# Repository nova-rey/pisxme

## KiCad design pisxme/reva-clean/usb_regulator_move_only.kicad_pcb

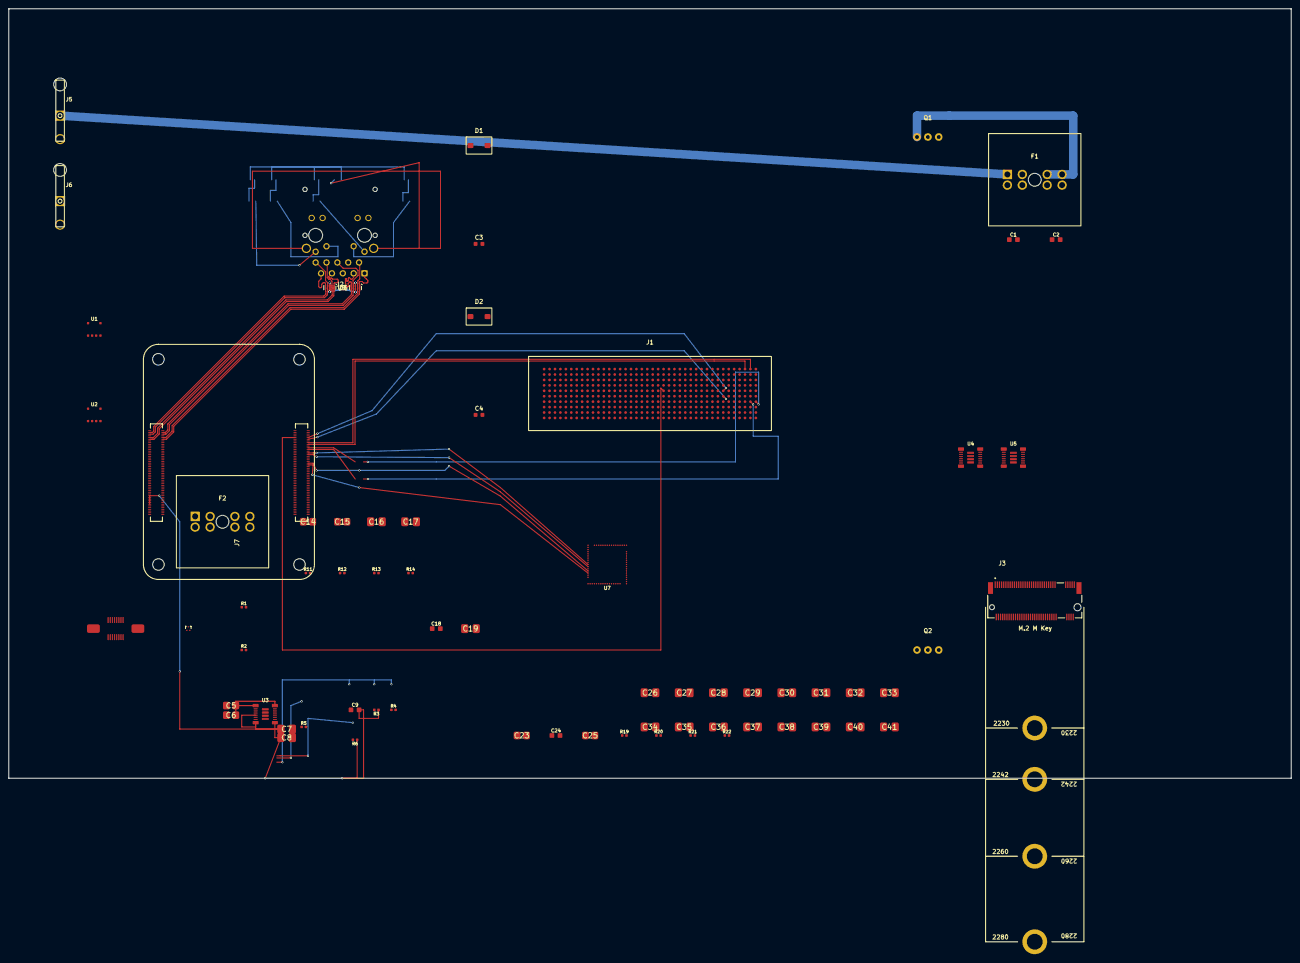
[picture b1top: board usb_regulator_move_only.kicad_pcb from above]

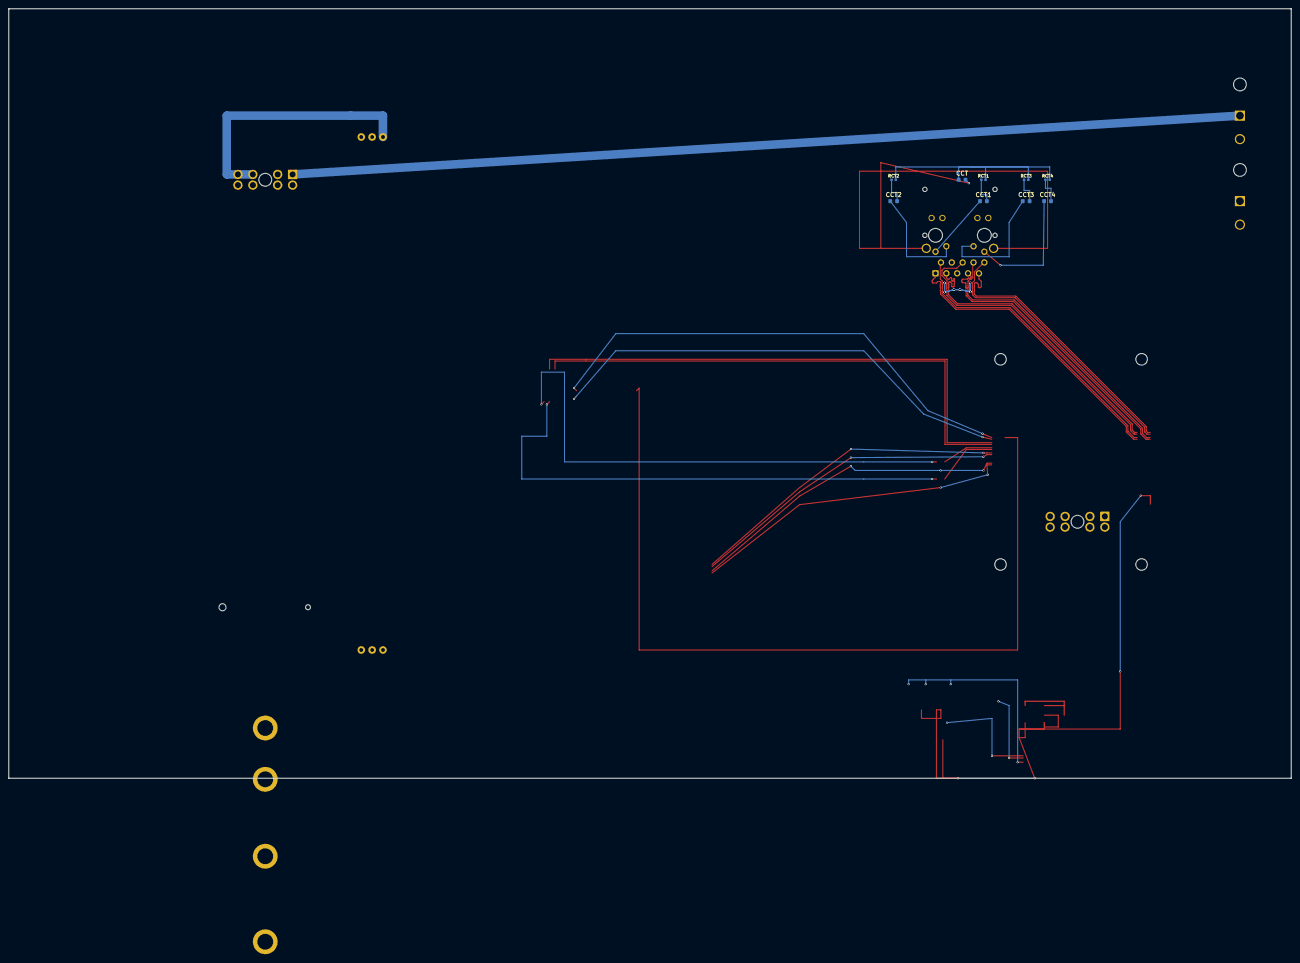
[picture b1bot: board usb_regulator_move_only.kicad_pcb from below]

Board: 6 copper layers, 300.0 x 180.0 mm, 80 parts (11 on the bottom side), 63 nets.

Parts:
C1, C2, C9, C18, C24: C_0805_2012Metric
C3, C4: C_0603_1608Metric
C5, C6, C14, C15, C23, C25: C_1206_3216Metric
C7, C8, C16, C17, C19, C26, C27, C28, C29, C30, C31, C32, C33, C34, C35, C36, C37, C38, C39, C40, C41: C_1210_3225Metric
CCT, CCT1, CCT2, CCT3, CCT4: C_0603_1608Metric
D1, D2: SMBJ18A; TVS_SMBJ18A_DO214AA
F1, F2: 178.6165.0001; ATO_FuseHolder_17861650001
J1: 74221-101LF; PiSXMeRevAClean_SXM2_74221_101LF
J2: A70-112-331N126; EDAC_A70_112_331N126
J3: JAE SM3ZS067U410ABR1000 B-key SATA socket; JAE_SM3ZS067U410ABR1000_BKEY
J4: Amphenol 10171746-00021LF USB-C USB2 SERVICE; USB_C_SERVICE_10171746
J5, J6: 0039300020; Molex_0039300020_5569_2P_RA
J7: Raspberry-Pi-5-Compute-Module; PiSXMeRevAClean_Raspberry_Pi_5_Compute_Module
MECH_M2_2280: JAE SM3ZS067U410ABR1000 / 2280 card envelope; M2_2280_RETENTION_ENVELOPE
Q1, Q2: CSD19536KCS; CSD19536KCS_TO220
R1, R2, R3, R4, R5, R6, R11, R12, R13, R14, R19, R20, R21, R22: R_0402_1005Metric
RCT1, RCT2, RCT3, RCT4: R_0402_1005Metric
U1, U2: LM74700QDBVRQ1; LM74700QDBVRQ1_SOT23_6
U3, U4, U5: TPSM63606RDLR; TPSM63606RDLR_RDL0020
U6, U9: TPD4EUSB30; USON-10_2.5x1.0mm_P0.5mm
U7: TUSB9261IPVP; TUSB9261IPVP_HTQFP64
U8: Texas_DRT_3

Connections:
12V_PROTECTED: C5.1, C6.1, C14.1, C15.1, C23.1, C24.1, C25.1, J1.A22, J1.A23, J1.A25, J1.A26, J1.A28, J1.A29, J1.A31, J1.A32, J1.A34, J1.A35, J1.A37, J1.A38, J1.A40, J1.B22, J1.B23, J1.B25, J1.B26, J1.B28, J1.B29, J1.B31, J1.B32, J1.B34, J1.B35, J1.B37, J1.B38, J1.B40, J1.C22, J1.C23, J1.C25, J1.C26, J1.C28, J1.C29, J1.C31, J1.C32, J1.C34, J1.C35, J1.C37, J1.C38, J1.C40, J1.D22, J1.D23, J1.D25, J1.D26, J1.D28, J1.D29, J1.D31, J1.D32, J1.D34, J1.D35, J1.D37, J1.D38, J1.D40, J1.E22, J1.E23, J1.E25, J1.E26, J1.E28, J1.E29, J1.E31, J1.E32, J1.E34, J1.E35, J1.E37, J1.E38, J1.E40, J1.F22, J1.F23, J1.F25, J1.F26, J1.F28, J1.F29, J1.F31, J1.F32, J1.F34, J1.F35, J1.F37, J1.F38, J1.F40, J1.G22, J1.G23, J1.G25, J1.G26, J1.G28, J1.G29, J1.G31, J1.G32, J1.G34, J1.G35, J1.G37, J1.G38, J1.G40, J1.H22, J1.H23, J1.H25, J1.H26, J1.H28, J1.H29, J1.H31, J1.H32, J1.H34, J1.H35, J1.H37, J1.H38, J1.H40, J1.J22, J1.J23, J1.J25, J1.J26, J1.J28, J1.J29, J1.J31, J1.J32, J1.J34, J1.J35, J1.J37, J1.J38, J1.J40, J1.K22, J1.K23, J1.K25, J1.K26, J1.K28, J1.K29, J1.K31, J1.K32, J1.K34, J1.K35, J1.K37, J1.K38, J1.K40, Q1.2, Q2.2, U1.4, U2.4, U3.1, U3.14, U3.16, U4.1, U4.14, U4.16, U5.1, U5.14, U5.16
/CORE_CM5/CM5_5V: C7.1, C8.1, C9.2, J7.77, J7.79, J7.81, J7.83, J7.85, J7.87, R3.1, R6.1, U3.5, U3.8, U3.9
/CORE_CM5/CM5_PER0_N: J1.A3, J7.118
/CORE_CM5/CM5_PER0_P: J1.A2, J7.116
/CORE_CM5/CM5_PERST: J1.E18, J7.109
/CORE_CM5/CM5_PET0_N: C2.1, J7.124
/CORE_CM5/CM5_PET0_P: C1.1, J7.122
/CORE_CM5/CM5_REFCLK_N: J1.F7, J7.112
/CORE_CM5/CM5_REFCLK_P: J1.E7, J7.110
/CORE_CM5/CM5_USB3_RX_N: J7.128, U7.42
/CORE_CM5/CM5_USB3_RX_P: J7.130, U7.43
/CORE_CM5/CM5_USB3_TX_N: J7.140, U7.45
/CORE_CM5/CM5_USB3_TX_P: J7.142, U7.46
/CORE_CM5/POWER_GND: J7.1, J7.2, J7.7, J7.8, J7.13, J7.14, J7.22, J7.23, J7.32, J7.33, J7.42, J7.43, J7.52, J7.53, J7.59, J7.60, J7.65, J7.66, J7.71, J7.74, J7.98, J7.107, J7.108, J7.113, J7.114, J7.119, J7.120, J7.125, J7.126, J7.131, J7.132, J7.137, J7.138, J7.144, J7.150, J7.155, J7.156, J7.161, J7.162, J7.167, J7.168, J7.173, J7.174, J7.179, J7.180, J7.185, J7.186, J7.191, J7.192, J7.197, J7.198
/ETHERNET/ETH_CT1: CCT1.1, J2.11
/ETHERNET/ETH_CT2: CCT2.1, J2.12
/ETHERNET/ETH_CT3: CCT3.1, J2.13
/ETHERNET/ETH_CT4: CCT4.1, J2.14
/ETHERNET/GBE_SHIELD: CCT.2, J2.19, J2.20
/POWER_INPUT/12V_IN_A: C3.2, F1.1, F1.2, F1.3, F1.4, J5.1, U1.3
/POWER_INPUT/12V_IN_B: C4.2, F2.1, F2.2, F2.3, F2.4, J6.1, U2.3
/POWER_INPUT/FUSED_12V_A: D1.1, F1.5, F1.6, F1.7, F1.8, Q1.1, U1.6
/POWER_INPUT/FUSED_12V_B: D2.1, F2.5, F2.6, F2.7, F2.8, Q2.1, U2.6
/POWER_INPUT/GATE_A: Q1.3, U1.5
/POWER_INPUT/GATE_B: Q2.3, U2.5
/POWER_INPUT/VCAP_A: C3.1, U1.1
/POWER_INPUT/VCAP_B: C4.1, U2.1
/REGULATORS/BRIDGE_1V1: C26.1, C27.1, C28.1, C29.1, C30.1, C31.1, C32.1, C33.1, C34.1, C35.1, C36.1, C37.1, C38.1, C39.1, C40.1, C41.1, R19.1, R22.1, U5.5, U5.8, U5.9
/REGULATORS/BRIDGE_3V3: C16.1, C17.1, C18.2, C19.1, R11.1, R14.1, U4.5, U4.8, U4.9
/REGULATORS/FB_BRIDGE_1V1: R19.2, R20.1, U5.10
/REGULATORS/FB_BRIDGE_3V3: C18.1, R11.2, R12.1, U4.10
/REGULATORS/FB_CM5_5V: C9.1, R3.2, R4.1, U3.10
/REGULATORS/NC: U3.15, U4.15, U5.15
/REGULATORS/PG_BRIDGE_1V1: R22.2, U5.13
/REGULATORS/PG_BRIDGE_3V3: R14.2, U4.13
/REGULATORS/PG_CM5_5V: R6.2, U3.13
/REGULATORS/RT_BRIDGE_1V1: R21.1, U5.12
/REGULATORS/RT_BRIDGE_3V3: R13.1, U4.12
/REGULATORS/RT_CM5_5V: R5.1, U3.12
/SERVICE/SERVICE_GND: J4.A1, J4.A4, J4.A5, J4.A6, J4.A7, J4.A9, J4.A12, J4.B1, J4.B4, J4.B5, J4.B6, J4.B7, J4.B9, J4.B12, R1.1, R1.2, R2.1, R2.2, U8.1, U8.2, U8.3
/STORAGE/BRIDGE_1V1: U7.3, U7.41
/STORAGE/BRIDGE_CFG: U7.1, U7.21
/STORAGE/BRIDGE_RESET: U7.2, U7.4
/STORAGE/BRIDGE_SATA_RX_N: J3.4, U7.5, U7.6, U7.7, U7.8, U7.9, U7.59
/STORAGE/BRIDGE_SATA_RX_P: J3.3, U7.60
/STORAGE/BRIDGE_SATA_TX_N: J3.2, U7.56
/STORAGE/BRIDGE_SATA_TX_P: J3.1, U7.57
/V100_PCIE/V100_PET0_N: C2.2, J1.G2
/V100_PCIE/V100_PET0_P: C1.2, J1.G1
CM5_GBE_TD0_N: J2.2, J7.10, U6.2 (D1-), U6.9
CM5_GBE_TD0_P: J2.1, J7.12, U6.1 (D1+), U6.10
CM5_GBE_TD1_N: J2.6, J7.6, U6.4 (D2+), U6.7
CM5_GBE_TD1_P: J2.3, J7.4, U6.5 (D2-), U6.6
CM5_GBE_TD2_N: J2.8, J7.9, U9.2 (D1-), U9.9
CM5_GBE_TD2_P: J2.7, J7.11, U9.1 (D1+), U9.10
CM5_GBE_TD3_N: J2.10, J7.5, U9.4 (D2+), U9.7
CM5_GBE_TD3_P: J2.9, J7.3, U9.5 (D2-), U9.6
ETH_CT_BRANCH_1: CCT1.2, RCT1.1
ETH_CT_BRANCH_2: CCT2.2, RCT2.1
ETH_CT_BRANCH_3: CCT3.2, RCT3.1
ETH_CT_BRANCH_4: CCT4.2, RCT4.1
ETH_CT_COMMON: CCT.1, RCT1.2, RCT2.2, RCT3.2, RCT4.2
POWER_GND: C5.2, C6.2, C7.2, C8.2, C14.2, C15.2, C16.2, C17.2, C19.2, C23.2, C24.2, C25.2, C26.2, C27.2, C28.2, C29.2, C30.2, C31.2, C32.2, C33.2, C34.2, C35.2, C36.2, C37.2, C38.2, C39.2, C40.2, C41.2, D1.2, D2.2, J1.A21, J1.A24, J1.A27, J1.A30, J1.A33, J1.A36, J1.A39, J1.B21, J1.B24, J1.B27, J1.B30, J1.B33, J1.B36, J1.B39, J1.C21, J1.C24, J1.C27, J1.C30, J1.C33, J1.C36, J1.C39, J1.D21, J1.D24, J1.D27, J1.D30, J1.D33, J1.D36, J1.D39, J1.E21, J1.E24, J1.E27, J1.E30, J1.E33, J1.E36, J1.E39, J1.F21, J1.F24, J1.F27, J1.F30, J1.F33, J1.F36, J1.F39, J1.G21, J1.G24, J1.G27, J1.G30, J1.G33, J1.G36, J1.G39, J1.H21, J1.H24, J1.H27, J1.H30, J1.H33, J1.H36, J1.H39, J1.J21, J1.J24, J1.J27, J1.J30, J1.J33, J1.J36, J1.J39, J1.K21, J1.K24, J1.K27, J1.K30, J1.K33, J1.K36, J1.K39, J3.6, J5.2, J6.2, R4.2, R5.2, R12.2, R13.2, R20.2, R21.2, U1.2, U2.2, U3.6, U3.11, U3.17, U3.18, U3.19, U3.20, U4.6, U4.11, U4.17, U4.18, U4.19, U4.20, U5.6, U5.11, U5.17, U5.18, U5.19, U5.20, U6.3 (GND), U6.8 (GND), U9.3 (GND), U9.8 (GND)

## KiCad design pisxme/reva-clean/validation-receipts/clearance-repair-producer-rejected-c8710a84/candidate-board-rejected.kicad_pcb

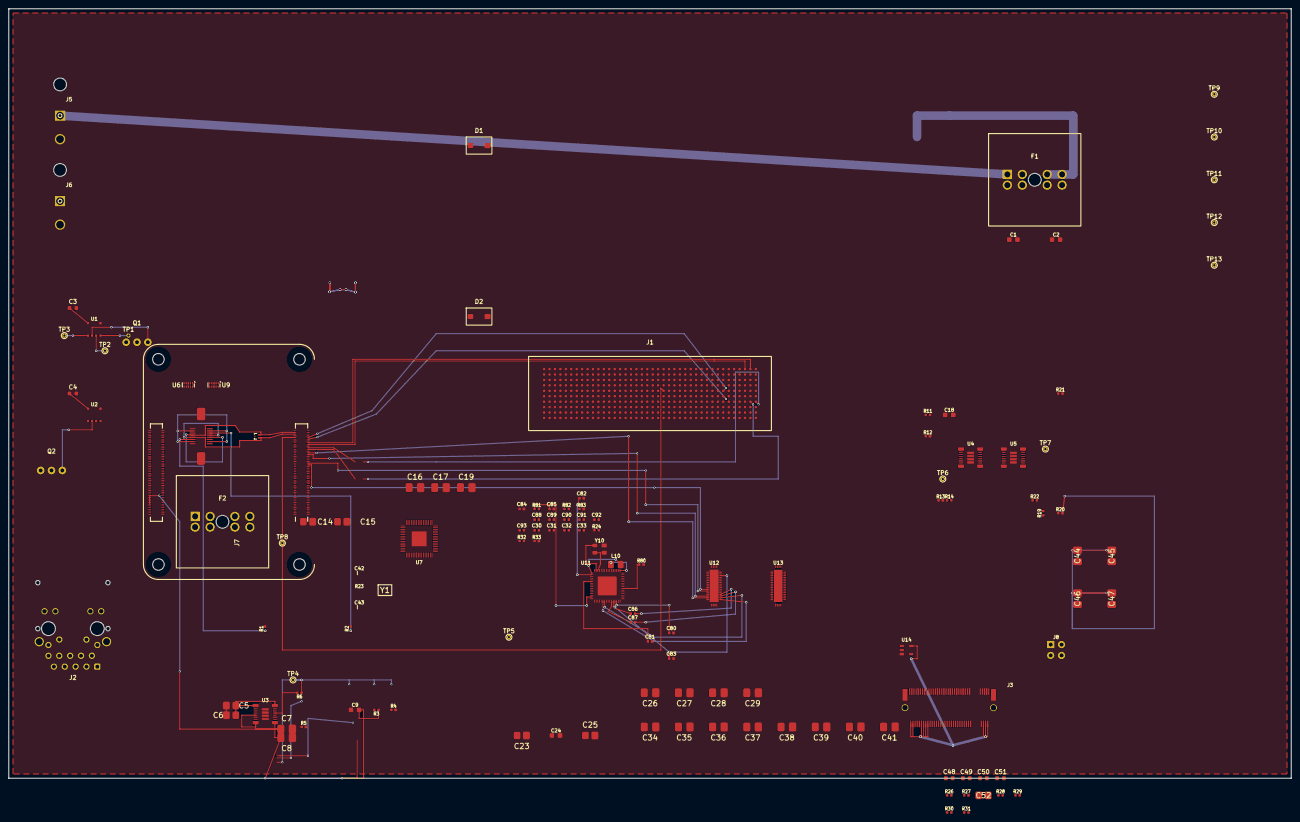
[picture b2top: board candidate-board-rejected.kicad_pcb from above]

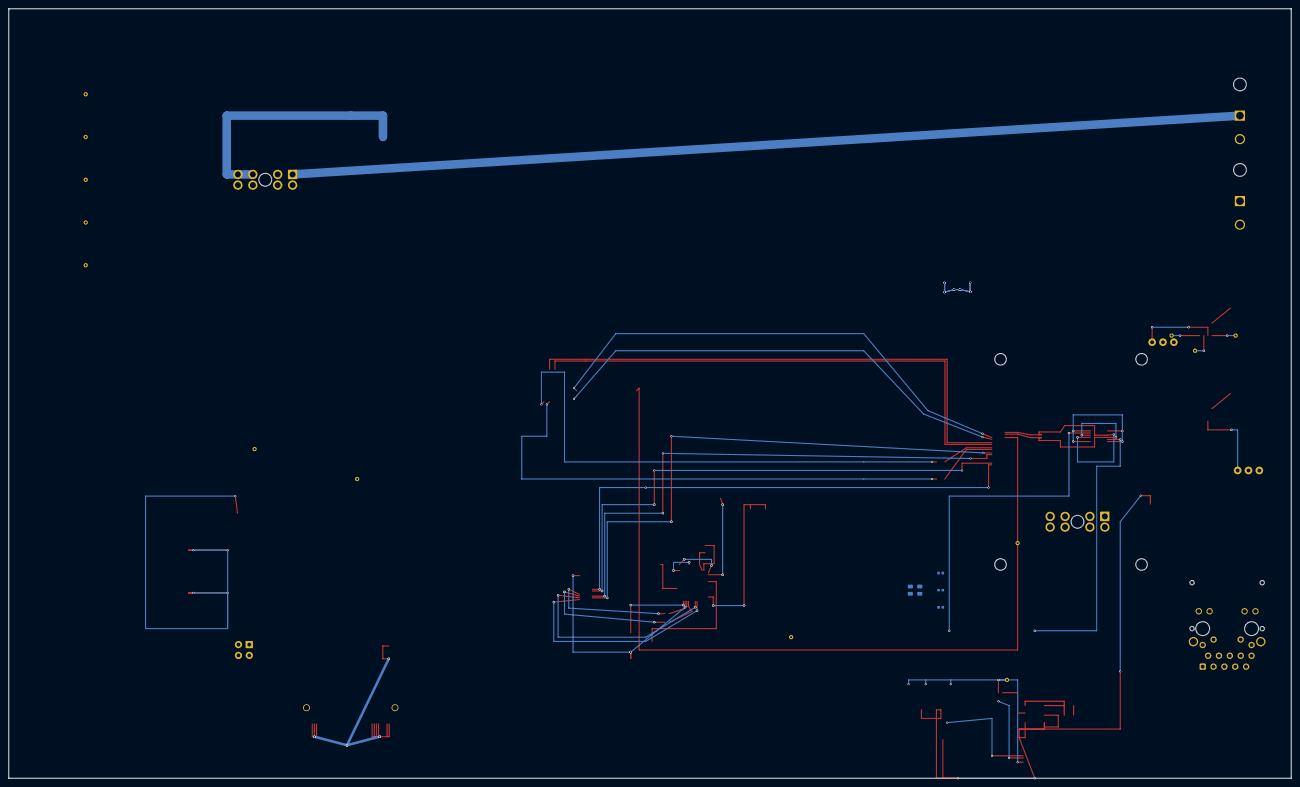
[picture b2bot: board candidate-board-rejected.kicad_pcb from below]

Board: 6 copper layers, 300.0 x 180.0 mm, 131 parts (15 on the bottom side), 136 nets.

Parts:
C1, C2, C9, C18, C24: C_0805_2012Metric
C3, C4, C48, C49, C50, C51: C_0603_1608Metric
C5, C6, C14, C15, C23, C25, C52: C_1206_3216Metric
C7, C8, C16, C17, C19, C26, C27, C28, C29, C34, C35, C36, C37, C38, C39, C40, C41, C44, C45, C46, C47: C_1210_3225Metric
C30, C31, C32, C33, C42, C43, C80, C81, C82, C83, C84, C85, C86, C87, C88, C89, C90, C91, C92, C93: C_0402_1005Metric
D1, D2: SMBJ18A; TVS_SMBJ18A_DO214AA
F1, F2: 178.6165.0001; ATO_FuseHolder_17861650001
J1: 74221-101LF; PiSXMeRevAClean_SXM2_74221_101LF
J2: A70-112-331N126; EDAC_A70_112_331N126
J3: 1-2199230-4; TE_1-2199230-4_MKEY
J4: Amphenol 10171746-00021LF USB-C USB2 SERVICE; USB_C_SERVICE_10171746
J5, J6: 0039300020; Molex_0039300020_5569_2P_RA
J7: Raspberry-Pi-5-Compute-Module; PiSXMeRevAClean_Raspberry_Pi_5_Compute_Module
J8: MODE_JUMPER_1x04
L10: 4.7uH; L_2520_6332Metric
MECH_M2_2280: JAE SM3ZS067U410ABR1000 / 2280 card envelope; M2_2280_RETENTION_ENVELOPE
Q1, Q2: CSD19536KCS; CSD19536KCS_TO220
R1, R2, R3, R4, R5, R6, R11, R12, R13, R14, R19, R20, R21, R22, R23, R24, R26, R27, R28, R29, R30, R31, R32, R33, R80, R81, R82, R83: R_0402_1005Metric
TP1, TP2, TP3, TP4, TP5, TP6, TP7, TP8, TP9, TP10, TP11, TP12, TP13: REV_A_PROBE; TestPoint_THTPad_D1.0mm_Drill0.5mm
U1, U2: LM74700QDBVRQ1; LM74700QDBVRQ1_SOT23_6
U3, U4, U5: TPSM63606RDLR; TPSM63606RDLR_RDL0020
U6, U9: TPD4EUSB30; USON-10_2.5x1.0mm_P0.5mm
U7: TUSB9261IPVP; TUSB9261IPVP_PVP0064A
U8: Texas_DRT_3
U11: JMS583_QFN64_8x8
U12: HD3SS6126_RUA0042A
U13: HD3SS3412_RUA0042A
U14: SOT-23-5
Y1: Crystal_3225_4Pad
Y10: 25MHz; Crystal_3225_4Pad

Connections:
12V_IN_A: C3.2, F1.1, F1.2, F1.3, F1.4, J5.1, TP1.1, U1.3
12V_IN_B: C4.2, F2.1, F2.2, F2.3, F2.4, J6.1, U2.3
12V_PROTECTED: C5.1, C6.1, C14.1, C15.1, C23.1, C24.1, C25.1, J1.A22, J1.A23, J1.A25, J1.A26, J1.A28, J1.A29, J1.A31, J1.A32, J1.A34, J1.A35, J1.A37, J1.A38, J1.A40, J1.B22, J1.B23, J1.B25, J1.B26, J1.B28, J1.B29, J1.B31, J1.B32, J1.B34, J1.B35, J1.B37, J1.B38, J1.B40, J1.C22, J1.C23, J1.C25, J1.C26, J1.C28, J1.C29, J1.C31, J1.C32, J1.C34, J1.C35, J1.C37, J1.C38, J1.C40, J1.D22, J1.D23, J1.D25, J1.D26, J1.D28, J1.D29, J1.D31, J1.D32, J1.D34, J1.D35, J1.D37, J1.D38, J1.D40, J1.E22, J1.E23, J1.E25, J1.E26, J1.E28, J1.E29, J1.E31, J1.E32, J1.E34, J1.E35, J1.E37, J1.E38, J1.E40, J1.F22, J1.F23, J1.F25, J1.F26, J1.F28, J1.F29, J1.F31, J1.F32, J1.F34, J1.F35, J1.F37, J1.F38, J1.F40, J1.G22, J1.G23, J1.G25, J1.G26, J1.G28, J1.G29, J1.G31, J1.G32, J1.G34, J1.G35, J1.G37, J1.G38, J1.G40, J1.H22, J1.H23, J1.H25, J1.H26, J1.H28, J1.H29, J1.H31, J1.H32, J1.H34, J1.H35, J1.H37, J1.H38, J1.H40, J1.J22, J1.J23, J1.J25, J1.J26, J1.J28, J1.J29, J1.J31, J1.J32, J1.J34, J1.J35, J1.J37, J1.J38, J1.J40, J1.K22, J1.K23, J1.K25, J1.K26, J1.K28, J1.K29, J1.K31, J1.K32, J1.K34, J1.K35, J1.K37, J1.K38, J1.K40, Q1.2, Q2.2, TP3.1, U1.4, U2.4, U3.1, U3.14, U3.16, U4.1, U4.14, U4.16, U5.1, U5.14, U5.16
AUTO_PEDET: J3.69 (AUTO_PEDET), J8.2 (AUTO_PEDET)
BRIDGE_1V1: C26.1, C27.1, C28.1, C29.1, C34.1, C35.1, C36.1, C37.1, C38.1, C39.1, C40.1, C41.1, C44.1, C45.1, C46.1, C47.1, R19.1, R22.1, U5.5, U5.8, U5.9, U7.1, U7.12, U7.19, U7.32, U7.33, U7.41, U7.47, U7.49, U7.55, U7.61, U7.63
BRIDGE_3V3: C16.1, C17.1, C18.2, C19.1, R11.1, R14.1, TP5.1, U4.5, U4.8, U4.9, U7.7, U7.24, U7.30, U7.31, U7.34, U7.40, U7.48, U7.51, U7.62
BRIDGE_R1: R24.1 (BRIDGE_R1), U7.38
BRIDGE_R1RTN: R24.2 (BRIDGE_R1RTN), U7.39
BRIDGE_SATA_RX_N: C33.2 (BRIDGE_SATA_RX_N), U7.59
BRIDGE_SATA_RX_P: C32.2 (BRIDGE_SATA_RX_P), U7.60
BRIDGE_SATA_TX_N: C31.2 (BRIDGE_SATA_TX_N), U7.56
BRIDGE_SATA_TX_P: C30.2 (BRIDGE_SATA_TX_P), U7.57
BRIDGE_USB_DM: U7.35, U12.32 (BRIDGE_USB_DM)
BRIDGE_USB_DP: U7.36, U12.31 (BRIDGE_USB_DP)
BRIDGE_USB_VBUS: R32.2 (BRIDGE_USB_VBUS), R33.1 (BRIDGE_USB_VBUS), U7.50
BRIDGE_VSSOSC: C42.2, C43.2, U7.53, Y1.2, Y1.4
BRIDGE_XI: C42.1, R23.1, U7.52, Y1.1
BRIDGE_XO: C43.1, R23.2, U7.54, Y1.3
CM5_5V: C7.1, C8.1, C9.2, J7.77, J7.79, J7.81, J7.83, J7.85, J7.87, R3.1, R6.1, R32.1 (CM5_5V), TP4.1, U3.5, U3.8, U3.9
CM5_GBE_TD0_N: J2.2, J7.10, U6.2 (D1-), U6.9
CM5_GBE_TD0_P: J2.1, J7.12, U6.1 (D1+), U6.10
CM5_GBE_TD1_N: J2.6, J7.6, U6.4 (D2+), U6.7
CM5_GBE_TD1_P: J2.3, J7.4, U6.5 (D2-), U6.6
CM5_GBE_TD2_N: J2.8, J7.9, U9.2 (D1-), U9.9
CM5_GBE_TD2_P: J2.7, J7.11, U9.1 (D1+), U9.10
CM5_GBE_TD3_N: J2.10, J7.5, U9.4 (D2+), U9.7
CM5_GBE_TD3_P: J2.9, J7.3, U9.5 (D2-), U9.6
CM5_PER0_N: J1.A3, J7.118
CM5_PER0_P: J1.A2, J7.116
CM5_PERST: J1.E18, J7.109, TP8.1
CM5_PET0_N: C2.1, J7.124
CM5_PET0_P: C1.1, J7.122
CM5_REFCLK_N: J1.F7, J7.112
CM5_REFCLK_P: J1.E7, J7.110
CM5_STORAGE_USB2_DM: J7.136, U12.7 (CM5_STORAGE_USB2_DM)
CM5_STORAGE_USB2_DP: J7.134, U12.8 (CM5_STORAGE_USB2_DP)
CM5_USB3_RX_N: J7.128, U7.42, U12.16 (CM5_USB3_RX_N)
CM5_USB3_RX_P: J7.130, U7.43, U12.15 (CM5_USB3_RX_P)
CM5_USB3_TX_N: J7.140, U7.45, U12.12 (CM5_USB3_TX_N)
CM5_USB3_TX_P: J7.142, U7.46, U12.11 (CM5_USB3_TX_P)
ETH_CT1: C48.1, J2.11
ETH_CT2: C49.1, J2.12
ETH_CT3: C50.1, J2.13
ETH_CT4: C51.1, J2.14
ETH_CT_BRANCH_1: C48.2, R26.1
ETH_CT_BRANCH_2: C49.2, R27.1
ETH_CT_BRANCH_3: C50.2, R28.1
ETH_CT_BRANCH_4: C51.2, R29.1
ETH_CT_COMMON: C52.1, R26.2, R27.2, R28.2, R29.2
ETH_LEDG: J7.15, R31.1
ETH_LEDY: J7.17, R30.1
ETH_POWER: J2.15, J2.17
FB_BRIDGE_1V1: R19.2, R20.1, U5.10
FB_BRIDGE_3V3: C18.1, R11.2, R12.1, U4.10
FB_CM5_5V: C9.1, R3.2, R4.1, U3.10
FUSED_12V_A: D1.1, F1.5, F1.6, F1.7, F1.8, Q1.1, TP2.1, U1.6
FUSED_12V_B: D2.1, F2.5, F2.6, F2.7, F2.8, Q2.1, U2.6
GATE_A: Q1.3, U1.5
GATE_B: Q2.3, U2.5
GBE_LED_G_K: J2.18, R31.2
GBE_LED_Y_K: J2.16, R30.2
GBE_SHIELD: C52.2, J2.19, J2.20
JMS_AVDD33: C80.1 (JMS_AVDD33), U11.19 (JMS_AVDD33)
JMS_AVDDL: C83.1 (JMS_AVDDL), J3.20 (JMS_AVDDL), J3.30 (JMS_AVDDL), J3.36 (JMS_AVDDL), J3.40 (JMS_AVDDL), J3.46 (JMS_AVDDL), U11.20 (JMS_AVDDL), U11.25 (JMS_AVDDL), U11.30 (JMS_AVDDL), U11.33 (JMS_AVDDL), U11.36 (JMS_AVDDL), U11.40 (JMS_AVDDL), U11.43 (JMS_AVDDL), U11.46 (JMS_AVDDL), U11.49 (JMS_AVDDL), U12.36 (JMS_AVDDL), U12.40 (JMS_AVDDL), U13.40 (JMS_AVDDL)
JMS_GPIO4_NC: J3.8 (JMS_GPIO4_NC), U11.8 (JMS_GPIO4_NC), U13.8 (JMS_GPIO4_NC)
JMS_PCIE_TXN0: C91.2 (JMS_PCIE_TXN0), U13.33 (JMS_PCIE_TXN0)
JMS_PCIE_TXN1: C93.2 (JMS_PCIE_TXN1), U13.24 (JMS_PCIE_TXN1)
JMS_PCIE_TXP0: C90.2 (JMS_PCIE_TXP0), U13.34 (JMS_PCIE_TXP0)
JMS_PCIE_TXP1: C92.2 (JMS_PCIE_TXP1), U13.25 (JMS_PCIE_TXP1)
JMS_RESET_N: C85.1 (JMS_RESET_N), R81.1 (JMS_RESET_N), U11.15 (JMS_RESET_N)
JMS_REXT: R80.1 (JMS_REXT), U11.39 (JMS_REXT)
JMS_SPI_SCK_DNP: U11.4 (JMS_SPI_SCK_DNP), U12.4 (JMS_SPI_SCK_DNP)
JMS_SPI_SI_DNP: U11.5 (JMS_SPI_SI_DNP), U12.5 (JMS_SPI_SI_DNP)
JMS_SPI_SO_DNP: U11.3 (JMS_SPI_SO_DNP), U12.3 (JMS_SPI_SO_DNP)
JMS_USB3_TXN: C87.2 (JMS_USB3_TXN), U12.24 (JMS_USB3_TXN)
JMS_USB3_TXP: C86.2 (JMS_USB3_TXP), U12.25 (JMS_USB3_TXP)
JMS_VBUS_SENSE: R82.2 (JMS_VBUS_SENSE), R83.1 (JMS_VBUS_SENSE), U11.10 (JMS_VBUS_SENSE)
JMS_VCCK: C82.1 (JMS_VCCK), U11.2 (JMS_VCCK), U11.31 (JMS_VCCK), U11.53 (JMS_VCCK), U12.2 (JMS_VCCK)
JMS_VCCO: C81.1 (JMS_VCCO), J3.6 (JMS_VCCO), J3.32 (JMS_VCCO), U11.6 (JMS_VCCO), U11.11 (JMS_VCCO), U11.32 (JMS_VCCO), U11.56 (JMS_VCCO)
JMS_VDDREG_5V: L10.2 (JMS_VDDREG_5V), U11.1 (JMS_VDDREG_5V), U12.1 (JMS_VDDREG_5V), U14.1 (JMS_VDDREG_5V)
JMS_XAVDDH: C84.1 (JMS_XAVDDH), U11.52 (JMS_XAVDDH)
LXO: L10.1 (LXO), U11.64 (LXO)
M2_PCIE_TXN2: J3.23 (M2_PCIE_TXN2), U13.12 (M2_PCIE_TXN2)
M2_PCIE_TXN3: J3.11 (M2_PCIE_TXN3), U13.16 (M2_PCIE_TXN3)
M2_PCIE_TXP2: J3.25 (M2_PCIE_TXP2), U13.11 (M2_PCIE_TXP2)
M2_PCIE_TXP3: J3.13 (M2_PCIE_TXP3), U13.15 (M2_PCIE_TXP3)
M2_SATA_A_N_PCIE_TXN0: J3.47 (M2_SATA_A_N_PCIE_TXN0), U13.3 (M2_SATA_A_N_PCIE_TXN0)
M2_SATA_A_P_PCIE_TXP0: J3.49 (M2_SATA_A_P_PCIE_TXP0), U13.2 (M2_SATA_A_P_PCIE_TXP0)
M2_SATA_B_N_PCIE_RXP0: J3.43 (M2_SATA_B_N_PCIE_RXP0), U13.7 (M2_SATA_B_N_PCIE_RXP0)
M2_SATA_B_P_PCIE_RXN0: J3.41 (M2_SATA_B_P_PCIE_RXN0), U13.6 (M2_SATA_B_P_PCIE_RXN0)
MODE_IN: J8.4 (MODE_IN), U14.2 (MODE_IN)
NC: U3.15, U4.15, U5.15
NC_18: U12.18 (NC_18), U13.18 (NC_18)
NC_26: J3.26 (NC_26), U13.26 (NC_26)
NC_28: J3.28 (NC_28), U13.28 (NC_28)
NC_39: U12.39 (NC_39), U13.39 (NC_39)
NC_41: U12.41 (NC_41), U13.41 (NC_41)
NC_42: J3.42 (NC_42), U12.42 (NC_42), U13.42 (NC_42)
PCIE_TXN0: C91.1 (PCIE_TXN0), U11.44 (PCIE_TXN0)
PCIE_TXN1: C93.1 (PCIE_TXN1), U11.37 (PCIE_TXN1)
PCIE_TXP0: C90.1 (PCIE_TXP0), U11.45 (PCIE_TXP0)
PCIE_TXP1: C92.1 (PCIE_TXP1), U11.38 (PCIE_TXP1)
PG_BRIDGE_1V1: R22.2, TP7.1, U5.13
PG_BRIDGE_3V3: R14.2, TP6.1, U4.13
PG_CM5_5V: R6.2, U3.13
POWER_GND: C5.2, C6.2, C7.2, C8.2, C14.2, C15.2, C16.2, C17.2, C19.2, C23.2, C24.2, C25.2, C26.2, C27.2, C28.2, C29.2, C34.2, C35.2, C36.2, C37.2, C38.2, C39.2, C40.2, C41.2, C44.2, C45.2, C46.2, C47.2, C80.2 (POWER_GND), C81.2 (POWER_GND), C82.2 (POWER_GND), C83.2 (POWER_GND), C84.2 (POWER_GND), C85.2 (POWER_GND), D1.2, D2.2, J1.A1, J1.A4, J1.A7, J1.A10, J1.A13, J1.A14, J1.A17, J1.A19, J1.A21, J1.A24, J1.A27, J1.A30, J1.A33, J1.A36, J1.A39, J1.B3, J1.B6, J1.B7, J1.B8, J1.B11, J1.B14, J1.B15, J1.B18, J1.B19, J1.B21, J1.B24, J1.B27, J1.B30, J1.B33, J1.B36, J1.B39, J1.C1, J1.C4, J1.C7, J1.C10, J1.C13, J1.C14, J1.C17, J1.C19, J1.C21, J1.C24, J1.C27, J1.C30, J1.C33, J1.C36, J1.C39, J1.D3, J1.D6, J1.D7, J1.D8, J1.D11, J1.D14, J1.D15, J1.D18, J1.D19, J1.D21, J1.D24, J1.D27, J1.D30, J1.D33, J1.D36, J1.D39, J1.E1, J1.E2, J1.E3, J1.E4, J1.E5, J1.E6, J1.E8, J1.E9, J1.E10, J1.E11, J1.E12, J1.E13, J1.E14, J1.E15, J1.E16, J1.E17, J1.E19, J1.E21, J1.E24, J1.E27, J1.E30, J1.E33, J1.E36, J1.E39, J1.F1, J1.F2, J1.F3, J1.F4, J1.F5, J1.F6, J1.F8, J1.F9, J1.F10, J1.F11, J1.F12, J1.F13, J1.F14, J1.F15, J1.F16, J1.F17, J1.F19, J1.F21, J1.F24, J1.F27, J1.F30, J1.F33, J1.F36, J1.F39, J1.G3, J1.G6, J1.G7, J1.G8, J1.G11, J1.G14, J1.G15, J1.G18, J1.G19, J1.G21, J1.G24, J1.G27, J1.G30, J1.G33, J1.G36, J1.G39, J1.H1, J1.H4, J1.H7, J1.H10, J1.H13, J1.H14, J1.H17, J1.H21, J1.H24, J1.H27, J1.H30, J1.H33, J1.H36, J1.H39, J1.J3, J1.J6, J1.J7, J1.J8, J1.J11, J1.J14, J1.J15, J1.J18, J1.J19, J1.J21, J1.J24, J1.J27, J1.J30, J1.J33, J1.J36, J1.J39, J1.K1, J1.K4, J1.K7, J1.K10, J1.K13, J1.K14, J1.K17, J1.K21, J1.K24, J1.K27, J1.K30, J1.K33, J1.K36, J1.K39, J3.3 (POWER_GND), J3.9 (POWER_GND), J3.15 (POWER_GND), J3.27 (POWER_GND), J3.33 (POWER_GND), J3.39 (POWER_GND), J3.45 (POWER_GND), J3.51 (POWER_GND), J3.57 (POWER_GND), J3.71 (POWER_GND), J3.73 (POWER_GND), J5.2, J6.2, J7.1, J7.2, J7.7, J7.8, J7.13, J7.14, J7.22, J7.23, J7.32, J7.33, J7.42, J7.43, J7.52, J7.53, J7.59, J7.60, J7.65, J7.66, J7.71, J7.74, J7.98, J7.107, J7.108, J7.113, J7.114, J7.119, J7.120, J7.125, J7.126, J7.131, J7.132, J7.137, J7.138, J7.144, J7.150, J7.155, J7.156, J7.161, J7.162, J7.167, J7.168, J7.173, J7.174, J7.179, J7.180, J7.185, J7.186, J7.191, J7.192, J7.197, J7.198, R4.2, R5.2, R12.2, R13.2, R20.2, R21.2, R33.2 (POWER_GND), R80.2 (POWER_GND), R83.2 (POWER_GND), TP9.1, U1.2, U2.2, U3.6, U3.11, U3.17, U3.18, U3.19, U3.20, U4.6, U4.11, U4.17, U4.18, U4.19, U4.20, U5.6, U5.11, U5.17, U5.18, U5.19, U5.20, U6.3 (GND), U6.8 (GND), U7.44, U7.58, U7.65, U9.3 (GND), U9.8 (GND), U11.60 (POWER_GND), U11.63 (POWER_GND), U12.10 (POWER_GND), U12.14 (POWER_GND), U12.17 (POWER_GND), U12.19 (POWER_GND), U12.21 (POWER_GND), U12.43 (POWER_GND), U13.1 (POWER_GND), U13.4 (POWER_GND), U13.10 (POWER_GND), U13.14 (POWER_GND), U13.17 (POWER_GND), U13.19 (POWER_GND), U13.21 (POWER_GND), U14.3 (POWER_GND), Y10.3 (POWER_GND), Y10.4 (POWER_GND)
RT_BRIDGE_1V1: R21.1, U5.12
RT_BRIDGE_3V3: R13.1, U4.12
RT_CM5_5V: R5.1, U3.12
SERVICE_GND: J4.A1, J4.A12, J4.B1, J4.B12, R1.2, R2.2, U8.3
SERVICE_RD_A: J4.A5, R1.1
SERVICE_RD_B: J4.B5, R2.1
SERVICE_USB2_DM: J4.A7, J4.B7, J7.103, U8.2
SERVICE_USB2_DP: J4.A6, J4.B6, J7.105, U8.1
SERVICE_VBUS_SENSE: J4.A4, J4.A9, J4.B4, J4.B9
STORAGE_3V3: J3.2 (M2_3V3), J3.4 (M2_3V3), J3.12 (M2_3V3), J3.14 (M2_3V3), J3.16 (M2_3V3), J3.18 (M2_3V3), J3.70 (M2_3V3), J3.72 (M2_3V3), J3.74 (M2_3V3), R81.2 (STORAGE_3V3), U12.13 (STORAGE_3V3), U12.20 (STORAGE_3V3), U12.30 (STORAGE_3V3), U13.5 (STORAGE_3V3), U13.13 (STORAGE_3V3), U13.20 (STORAGE_3V3), U13.30 (STORAGE_3V3), U14.5 (STORAGE_3V3)
STORAGE_SEL: U12.9 (STORAGE_SEL), U13.9 (STORAGE_SEL), U14.4 (STORAGE_SEL)
TUSB_SATA_RXN: C33.1 (TUSB_SATA_RXN), U13.35 (TUSB_SATA_RXN)
TUSB_SATA_RXP: C32.1 (TUSB_SATA_RXP), U13.36 (TUSB_SATA_RXP)
TUSB_SATA_TXN: C31.1 (TUSB_SATA_TXN), U13.37 (TUSB_SATA_TXN)
TUSB_SATA_TXP: C30.1 (TUSB_SATA_TXP), U13.38 (TUSB_SATA_TXP)
USB_DM: U11.17 (USB_DM), U12.34 (USB_DM)
USB_DP: U11.18 (USB_DP), U12.33 (USB_DP)
USB_RXN1: U11.27 (USB_RXN1), U12.22 (USB_RXN1)
USB_RXP1: U11.26 (USB_RXP1), U12.23 (USB_RXP1)
USB_TXN1: C87.1 (USB_TXN1), U11.22 (USB_TXN1)
USB_TXN2: C89.1 (USB_TXN2), U11.23 (USB_TXN2)
USB_TXP1: C86.1 (USB_TXP1), U11.21 (USB_TXP1)
USB_TXP2: C88.1 (USB_TXP2), U11.24 (USB_TXP2)
V100_PET0_N: C2.2, J1.G2
V100_PET0_P: C1.2, J1.G1
VBUS: R82.1 (VBUS), U11.16 (VBUS)
VCAP_A: C3.1, U1.1
VCAP_B: C4.1, U2.1
XIN: U11.50 (XIN), Y10.1 (XIN)
XOUT: U11.51 (XOUT), Y10.2 (XOUT)

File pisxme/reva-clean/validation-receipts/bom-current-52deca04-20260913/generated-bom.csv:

"Refs","Value","Footprint","Qty","DNP"
"C1","220nF X7R 50V","Capacitor_SMD:C_0805_2012Metric","1",""
"C2","220nF X7R 50V","Capacitor_SMD:C_0805_2012Metric","1",""
"C3","100nF VCAP A","PiSXMeRevAClean:C_0603_1608Metric","1",""
"C4","100nF VCAP B","PiSXMeRevAClean:C_0603_1608Metric","1",""
"C5","10uF 50V","PiSXMeRevAClean:C_1206_3216Metric","1",""
"C6","10uF 50V","PiSXMeRevAClean:C_1206_3216Metric","1",""
"C7","22uF","PiSXMeRevAClean:C_1210_3225Metric","1",""
"C8","22uF","PiSXMeRevAClean:C_1210_3225Metric","1",""
"C9","22pF","PiSXMeRevAClean:C_0805_2012Metric","1",""
"C14","10uF 50V","PiSXMeRevAClean:C_1206_3216Metric","1",""
"C15","10uF 50V","PiSXMeRevAClean:C_1206_3216Metric","1",""
"C16","22uF","PiSXMeRevAClean:C_1210_3225Metric","1",""
"C17","22uF","PiSXMeRevAClean:C_1210_3225Metric","1",""
"C18","47pF","PiSXMeRevAClean:C_0805_2012Metric","1",""
"C19","22uF","PiSXMeRevAClean:C_1210_3225Metric","1",""
"C23","10uF 50V","PiSXMeRevAClean:C_1206_3216Metric","1",""
"C24","1uF","PiSXMeRevAClean:C_0805_2012Metric","1",""
"C25","10uF 50V","PiSXMeRevAClean:C_1206_3216Metric","1",""
"C26","22uF","PiSXMeRevAClean:C_1210_3225Metric","1",""
"C27","22uF","PiSXMeRevAClean:C_1210_3225Metric","1",""
"C28","22uF","PiSXMeRevAClean:C_1210_3225Metric","1",""
"C29","22uF","PiSXMeRevAClean:C_1210_3225Metric","1",""
"C30","100nF","PiSXMeRevAClean:C_0402_1005Metric","1",""
"C31","100nF","PiSXMeRevAClean:C_0402_1005Metric","1",""
"C32","100nF","PiSXMeRevAClean:C_0402_1005Metric","1",""
"C33","100nF","PiSXMeRevAClean:C_0402_1005Metric","1",""
"C34","22uF","PiSXMeRevAClean:C_1210_3225Metric","1",""
"C35","22uF","PiSXMeRevAClean:C_1210_3225Metric","1",""
"C36","22uF","PiSXMeRevAClean:C_1210_3225Metric","1",""
"C37","22uF","PiSXMeRevAClean:C_1210_3225Metric","1",""
"C38","22uF","PiSXMeRevAClean:C_1210_3225Metric","1",""
"C39","22uF","PiSXMeRevAClean:C_1210_3225Metric","1",""
"C40","22uF","PiSXMeRevAClean:C_1210_3225Metric","1",""
"C41","22uF","PiSXMeRevAClean:C_1210_3225Metric","1",""
"C42","18pF","PiSXMeRevAClean:C_0402_1005Metric","1",""
"C43","18pF","PiSXMeRevAClean:C_0402_1005Metric","1",""
"C44","22uF","PiSXMeRevAClean:C_1210_3225Metric","1",""
"C45","22uF","PiSXMeRevAClean:C_1210_3225Metric","1",""
"C46","22uF","PiSXMeRevAClean:C_1210_3225Metric","1",""
"C47","22uF","PiSXMeRevAClean:C_1210_3225Metric","1",""
"C48","22nF 100V","PiSXMeRevAClean:C_0603_1608Metric","1",""
"C49","22nF 100V","PiSXMeRevAClean:C_0603_1608Metric","1",""
"C50","22nF 100V","PiSXMeRevAClean:C_0603_1608Metric","1",""
"C51","22nF 100V","PiSXMeRevAClean:C_0603_1608Metric","1",""
"C52","1nF 2kV","PiSXMeRevAClean:C_1206_3216Metric","1",""
"C80","4.7uF","PiSXMeRevAClean:C_0603_1608Metric","1",""
"C81","100n","PiSXMeRevAClean:C_0402_1005Metric","1",""
"C82","100n","PiSXMeRevAClean:C_0402_1005Metric","1",""
"C83","100n","PiSXMeRevAClean:C_0402_1005Metric","1",""
"C84","100n","PiSXMeRevAClean:C_0402_1005Metric","1",""
"C85","100n reset delay","PiSXMeRevAClean:C_0402_1005Metric","1",""
"C86","100n USB TX1P","PiSXMeRevAClean:C_0402_1005Metric","1",""
"C87","100n USB TX1N","PiSXMeRevAClean:C_0402_1005Metric","1",""
"C88","100n USB TX2P","PiSXMeRevAClean:C_0402_1005Metric","1",""
"C89","100n USB TX2N","PiSXMeRevAClean:C_0402_1005Metric","1",""
"C90","220n PCIe TX0P","PiSXMeRevAClean:C_0402_1005Metric","1",""
"C91","220n PCIe TX0N","PiSXMeRevAClean:C_0402_1005Metric","1",""
"C92","220n PCIe TX1P","PiSXMeRevAClean:C_0402_1005Metric","1",""
"C93","220n PCIe TX1N","PiSXMeRevAClean:C_0402_1005Metric","1",""
"D1","SMBJ18A","PiSXMeRevAClean:TVS_SMBJ18A_DO214AA","1",""
"D2","SMBJ18A","PiSXMeRevAClean:TVS_SMBJ18A_DO214AA","1",""
"F1","0297015.U / 178.6165.0001","PiSXMeRevAClean:ATO_FuseHolder_17861650001","1",""
"F2","0297015.U / 178.6165.0001","PiSXMeRevAClean:ATO_FuseHolder_17861650001","1",""
"J1","Amphenol 74221-101LF Rev-W","PiSXMeRevAClean:PiSXMeRevAClean_SXM2_74221_101LF","1",""
"J2","A70-112-331N126","PiSXMeRevAClean:EDAC_A70_112_331N126","1",""
"J3","1-2199230-4","PiSXMeRevAClean:TE_1-2199230-4_MKEY","1",""
"J4","10171746-00021LF","PiSXMeRevAClean:USB_C_SERVICE_10171746","1",""
"J5","0039300020","PiSXMeRevAClean:Molex_0039300020_5569_2P_RA","1",""
"J6","0039300020","PiSXMeRevAClean:Molex_0039300020_5569_2P_RA","1",""
"J7","ComputeModule5-CM5","PiSXMeRevAClean:PiSXMeRevAClean_Raspberry_Pi_5_Compute_Module","1",""
"J8","AUTO / FORCE SATA / FORCE NVMe","PiSXMeRevAClean:MODE_JUMPER_1x04","1",""
"L10","4.7uH","PiSXMeRevAClean:L_2520_6332Metric","1",""
"Q1","CSD19536KCS","PiSXMeRevAClean:CSD19536KCS_TO220","1",""
"Q2","CSD19536KCS","PiSXMeRevAClean:CSD19536KCS_TO220","1",""
"R1","5.1k Rd","PiSXMeRevAClean:R_0402_1005Metric","1",""
"R2","5.1k Rd","PiSXMeRevAClean:R_0402_1005Metric","1",""
"R3","40.2k","PiSXMeRevAClean:R_0402_1005Metric","1",""
"R4","10k","PiSXMeRevAClean:R_0402_1005Metric","1",""
"R5","13k","PiSXMeRevAClean:R_0402_1005Metric","1",""
"R6","100k","PiSXMeRevAClean:R_0402_1005Metric","1",""
"R11","23.2k","PiSXMeRevAClean:R_0402_1005Metric","1",""
"R12","10k","PiSXMeRevAClean:R_0402_1005Metric","1",""
"R13","27k","PiSXMeRevAClean:R_0402_1005Metric","1",""
"R14","100k","PiSXMeRevAClean:R_0402_1005Metric","1",""
"R19","1k","PiSXMeRevAClean:R_0402_1005Metric","1",""
"R20","10k","PiSXMeRevAClean:R_0402_1005Metric","1",""
"R21","2k","PiSXMeRevAClean:R_0402_1005Metric","1",""
"R22","100k","PiSXMeRevAClean:R_0402_1005Metric","1",""
"R23","1M","PiSXMeRevAClean:R_0402_1005Metric","1",""
"R24","10K","PiSXMeRevAClean:R_0402_1005Metric","1",""
"R26","75R","PiSXMeRevAClean:R_0402_1005Metric","1",""
"R27","75R","PiSXMeRevAClean:R_0402_1005Metric","1",""
"R28","75R","PiSXMeRevAClean:R_0402_1005Metric","1",""
"R29","75R","PiSXMeRevAClean:R_0402_1005Metric","1",""
"R30","470R","PiSXMeRevAClean:R_0402_1005Metric","1",""
"R31","470R","PiSXMeRevAClean:R_0402_1005Metric","1",""
"R32","90.9K","PiSXMeRevAClean:R_0402_1005Metric","1",""
"R33","10K","PiSXMeRevAClean:R_0402_1005Metric","1",""
"R80","12k 1%","PiSXMeRevAClean:R_0402_1005Metric","1",""
"R81","10k reset pullup","PiSXMeRevAClean:R_0402_1005Metric","1",""
"R82","100k VBUS top","PiSXMeRevAClean:R_0402_1005Metric","1",""
"R83","100k VBUS bottom","PiSXMeRevAClean:R_0402_1005Metric","1",""
"U1","LM74700QDBVRQ1","PiSXMeRevAClean:LM74700QDBVRQ1_SOT23_6","1",""
"U2","LM74700QDBVRQ1","PiSXMeRevAClean:LM74700QDBVRQ1_SOT23_6","1",""
"U3","TPSM63606RDLR","PiSXMeRevAClean:TPSM63606RDLR_RDL0020","1",""
"U4","TPSM63606RDLR","PiSXMeRevAClean:TPSM63606RDLR_RDL0020","1",""
"U5","TPSM63606RDLR","PiSXMeRevAClean:TPSM63606RDLR_RDL0020","1",""
"U6","TPD4EUSB30DQAR","PiSXMeRevAClean:USON-10_2.5x1.0mm_P0.5mm","1",""
"U7","TUSB9261IPVP","PiSXMeRevAClean:TUSB9261IPVP_PVP0064A","1",""
"U8","TPD2EUSB30DRTR","PiSXMeRevAClean:Texas_DRT_3","1",""
"U9","TPD4EUSB30DQAR","PiSXMeRevAClean:USON-10_2.5x1.0mm_P0.5mm","1",""
"U11","JMS583-QHFA3A","PiSXMeRevAClean:JMS583_QFN64_8x8","1",""
"U12","HD3SS6126RUAR","PiSXMeRevAClean:HD3SS6126_RUA0042A","1",""
"U13","HD3SS3412RUAR","PiSXMeRevAClean:HD3SS3412_RUA0042A","1",""
"U14","SN74LVC1G17DBVR","Package_TO_SOT_SMD:SOT-23-5","1",""
"Y1","ECS-400-18-33-JGN-TR3","PiSXMeRevAClean:Crystal_3225_4Pad","1",""
"Y10","25MHz +/-30ppm","PiSXMeRevAClean:Crystal_3225_4Pad","1",""
